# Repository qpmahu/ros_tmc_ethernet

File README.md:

# ros_tmc_ethernet
ROS node with ethernet TCP/UDP and TMC2208 via PIC18F24K50

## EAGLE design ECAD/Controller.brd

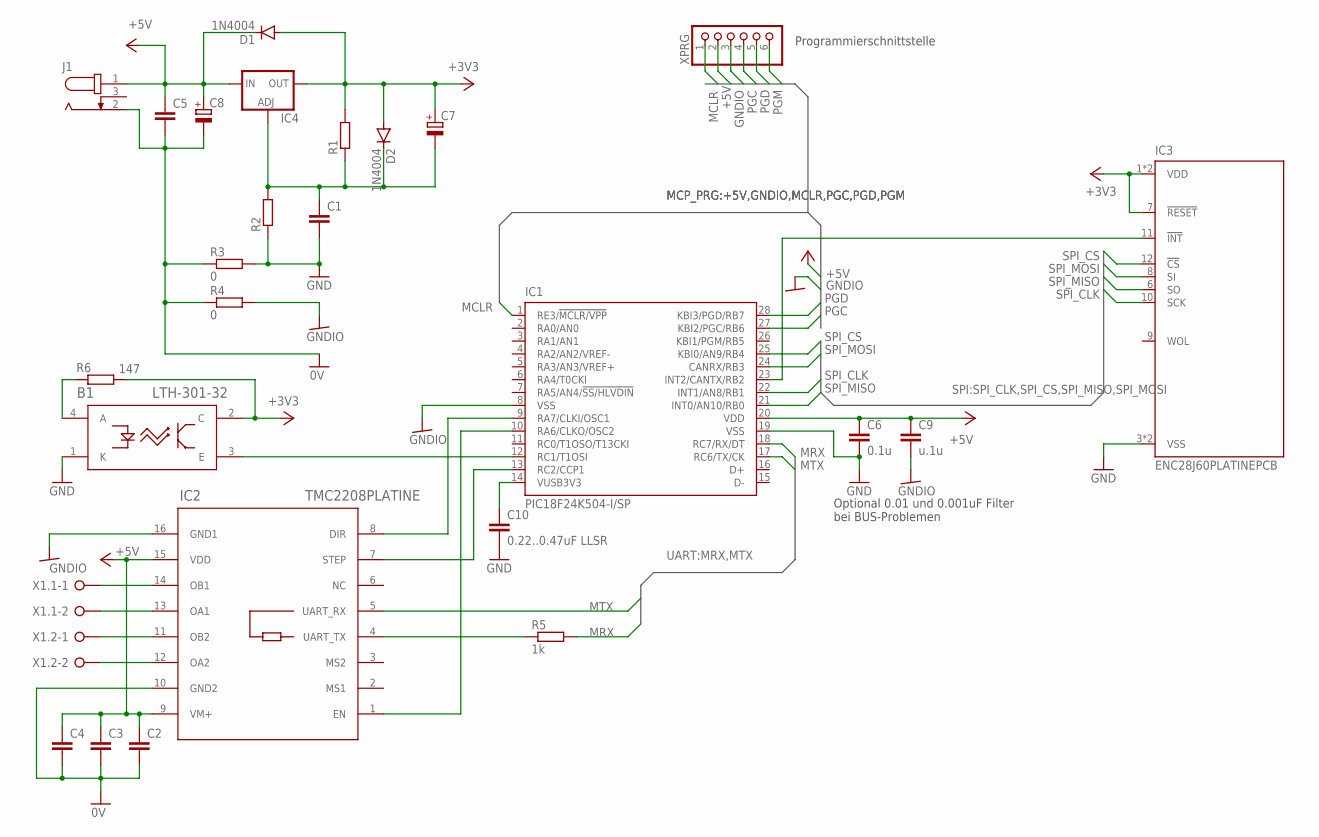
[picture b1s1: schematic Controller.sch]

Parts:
B1: LTH-301-32; LTH-301-32_LTO
C1, C2, C3, C4, C5: C-EU025_050-025X075; C025_050-025X075
C6: 0.1u; C025_050-025X075
C7, C8: CPOL-EUE2.5-6; E2,5-6
C9: u.1u; C025_050-025X075
C10: 0.22..0.47uF LLSR; C025_050-025X075
D1, D2: 1N4004; DO41-10
IC1: PIC18F24K504-I/SP; DIL28-3
IC2: TMC2208PLATINE; 2X08_TMCBOARD
IC3: ENC28J60PLATINEPCB; ENCPLATINE
IC4: LM317TO220; 317TL
J1: JACK-PLUG2,5; SPC4078
R1, R2: R-EU_0207/10; 0207/10
R3, R4: 0; R0603
R5: 1k; R0603
R6: 147; 0207/10
X1.1, X1.2: W237-02P; W237-132
XPRG: PINHD-1X6/90; 1X06/90

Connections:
0V: C2.2, C3.2, C4.2, C5.2, C8.-, IC2.10 (GND2), J1.2, R3.1, R4.1
+3V3: B1.2 (C), C7.+, D1.A, D2.A, IC3.1 (VDD), IC3.2 (VDD), IC3.7 (!RESET), IC4.2 (OUT), R1.2, R6.2
+5V: C2.1, C3.1, C4.1, C5.1, C6.1, C8.+, C9.1, D1.C, IC1.20 (VDD), IC2.9 (VM+), IC2.15 (VDD), IC4.3 (IN), J1.1, XPRG.2
GND: B1.1 (K), C1.2, C6.2, C10.2, IC1.19 (VSS), IC3.3 (VSS), IC3.4 (VSS), R2.1, R3.2
GNDIO: C9.2, IC1.8 (VSS), IC2.16 (GND1), R4.2, XPRG.3
MCLR: IC1.1 (RE3/!MCLR/VPP), XPRG.1
MRX: IC1.18 (RC7/RX/DT), R5.2
MTX: IC1.17 (RC6/TX/CK), IC2.5 (UART_RX)
unnamed: IC2.4 (UART_TX), R5.1
unnamed: IC1.13 (RC2/CCP1), IC2.7 (STEP)
unnamed: C1.1, C7.-, D2.C, IC4.1 (ADJ), R1.1, R2.2
unnamed: IC2.14 (OB1), X1.1.1
unnamed: IC1.23 (INT2/CANTX/RB2), IC3.11 (!INT)
unnamed: IC1.10 (RA6/CLKO/OSC2), IC2.1 (EN)
unnamed: IC1.9 (RA7/CLKI/OSC1), IC2.8 (DIR)
unnamed: IC2.13 (OA1), X1.1.2
unnamed: IC2.11 (OB2), X1.2.1
unnamed: IC2.12 (OA2), X1.2.2
unnamed: C10.1, IC1.14 (VUSB3V3)
unnamed: B1.3 (E), IC1.12 (RC1/T1OSI)
unnamed: B1.4 (A), R6.1
PGC: IC1.27 (KBI2/PGC/RB6), XPRG.4
PGD: IC1.28 (KBI3/PGD/RB7), XPRG.5
PGM: XPRG.6
SPI_CLK: IC1.22 (INT1/AN8/RB1), IC3.10 (SCK)
SPI_CS: IC1.25 (KBI0/AN9/RB4), IC3.12 (!CS)
SPI_MISO: IC1.21 (INT0/AN10/RB0), IC3.6 (SO)
SPI_MOSI: IC1.24 (CANRX/RB3), IC3.8 (SI)

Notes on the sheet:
Programmierschnittstelle
Optional 0.01 und 0.001uF Filter bei BUS-Problemen

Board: 2 copper layers, 27 parts (0 on the bottom side), 27 nets, no tracks yet.

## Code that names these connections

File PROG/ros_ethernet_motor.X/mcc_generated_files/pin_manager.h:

/**
  @Generated Pin Manager Header File

  @Company:
    Microchip Technology Inc.

  @File Name:
    pin_manager.h

  @Summary:
    This is the Pin Manager file generated using PIC10 / PIC12 / PIC16 / PIC18 MCUs

  @Description
    This header file provides APIs for driver for .
    Generation Information :
        Product Revision  :  PIC10 / PIC12 / PIC16 / PIC18 MCUs - 1.81.4
        Device            :  PIC18F24K50
        Driver Version    :  2.11
    The generated drivers are tested against the following:
        Compiler          :  XC8 2.20 and above
        MPLAB 	          :  MPLAB X 5.40	
*/

/*
    (c) 2018 Microchip Technology Inc. and its subsidiaries. 
    
    Subject to your compliance with these terms, you may use Microchip software and any 
    derivatives exclusively with Microchip products. It is your responsibility to comply with third party 
    license terms applicable to your use of third party software (including open source software) that 
    may accompany Microchip software.
    
    THIS SOFTWARE IS SUPPLIED BY MICROCHIP "AS IS". NO WARRANTIES, WHETHER 
    EXPRESS, IMPLIED OR STATUTORY, APPLY TO THIS SOFTWARE, INCLUDING ANY 
    IMPLIED WARRANTIES OF NON-INFRINGEMENT, MERCHANTABILITY, AND FITNESS 
    FOR A PARTICULAR PURPOSE.
    
    IN NO EVENT WILL MICROCHIP BE LIABLE FOR ANY INDIRECT, SPECIAL, PUNITIVE, 
    INCIDENTAL OR CONSEQUENTIAL LOSS, DAMAGE, COST OR EXPENSE OF ANY KIND 
    WHATSOEVER RELATED TO THE SOFTWARE, HOWEVER CAUSED, EVEN IF MICROCHIP 
    HAS BEEN ADVISED OF THE POSSIBILITY OR THE DAMAGES ARE FORESEEABLE. TO 
    THE FULLEST EXTENT ALLOWED BY LAW, MICROCHIP'S TOTAL LIABILITY ON ALL 
    CLAIMS IN ANY WAY RELATED TO THIS SOFTWARE WILL NOT EXCEED THE AMOUNT 
    OF FEES, IF ANY, THAT YOU HAVE PAID DIRECTLY TO MICROCHIP FOR THIS 
    SOFTWARE.
*/

#ifndef PIN_MANAGER_H
#define PIN_MANAGER_H

/**
  Section: Included Files
*/

#include <xc.h>

#define INPUT   1
#define OUTPUT  0

#define HIGH    1
#define LOW     0

#define ANALOG      1
#define DIGITAL     0

#define PULL_UP_ENABLED      1
#define PULL_UP_DISABLED     0

// get/set RB0 procedures
#define RB0_SetHigh()            do { LATBbits.LATB0 = 1; } while(0)
#define RB0_SetLow()             do { LATBbits.LATB0 = 0; } while(0)
#define RB0_Toggle()             do { LATBbits.LATB0 = ~LATBbits.LATB0; } while(0)
#define RB0_GetValue()              PORTBbits.RB0
#define RB0_SetDigitalInput()    do { TRISBbits.TRISB0 = 1; } while(0)
#define RB0_SetDigitalOutput()   do { TRISBbits.TRISB0 = 0; } while(0)
#define RB0_SetPullup()             do { WPUBbits.WPUB0 = 1; } while(0)
#define RB0_ResetPullup()           do { WPUBbits.WPUB0 = 0; } while(0)
#define RB0_SetAnalogMode()         do { ANSELBbits.ANSB0 = 1; } while(0)
#define RB0_SetDigitalMode()        do { ANSELBbits.ANSB0 = 0; } while(0)

// get/set RB1 procedures
#define RB1_SetHigh()            do { LATBbits.LATB1 = 1; } while(0)
#define RB1_SetLow()             do { LATBbits.LATB1 = 0; } while(0)
#define RB1_Toggle()             do { LATBbits.LATB1 = ~LATBbits.LATB1; } while(0)
#define RB1_GetValue()              PORTBbits.RB1
#define RB1_SetDigitalInput()    do { TRISBbits.TRISB1 = 1; } while(0)
#define RB1_SetDigitalOutput()   do { TRISBbits.TRISB1 = 0; } while(0)
#define RB1_SetPullup()             do { WPUBbits.WPUB1 = 1; } while(0)
#define RB1_ResetPullup()           do { WPUBbits.WPUB1 = 0; } while(0)
#define RB1_SetAnalogMode()         do { ANSELBbits.ANSB1 = 1; } while(0)
#define RB1_SetDigitalMode()        do { ANSELBbits.ANSB1 = 0; } while(0)

// get/set RB2 procedures
#define RB2_SetHigh()            do { LATBbits.LATB2 = 1; } while(0)
#define RB2_SetLow()             do { LATBbits.LATB2 = 0; } while(0)
#define RB2_Toggle()             do { LATBbits.LATB2 = ~LATBbits.LATB2; } while(0)
#define RB2_GetValue()              PORTBbits.RB2
#define RB2_SetDigitalInput()    do { TRISBbits.TRISB2 = 1; } while(0)
#define RB2_SetDigitalOutput()   do { TRISBbits.TRISB2 = 0; } while(0)
#define RB2_SetPullup()             do { WPUBbits.WPUB2 = 1; } while(0)
#define RB2_ResetPullup()           do { WPUBbits.WPUB2 = 0; } while(0)
#define RB2_SetAnalogMode()         do { ANSELBbits.ANSB2 = 1; } while(0)
#define RB2_SetDigitalMode()        do { ANSELBbits.ANSB2 = 0; } while(0)

// get/set RB3 procedures
#define RB3_SetHigh()            do { LATBbits.LATB3 = 1; } while(0)
#define RB3_SetLow()             do { LATBbits.LATB3 = 0; } while(0)
#define RB3_Toggle()             do { LATBbits.LATB3 = ~LATBbits.LATB3; } while(0)
#define RB3_GetValue()              PORTBbits.RB3
#define RB3_SetDigitalInput()    do { TRISBbits.TRISB3 = 1; } while(0)
#define RB3_SetDigitalOutput()   do { TRISBbits.TRISB3 = 0; } while(0)
#define RB3_SetPullup()             do { WPUBbits.WPUB3 = 1; } while(0)
#define RB3_ResetPullup()           do { WPUBbits.WPUB3 = 0; } while(0)
#define RB3_SetAnalogMode()         do { ANSELBbits.ANSB3 = 1; } while(0)
#define RB3_SetDigitalMode()        do { ANSELBbits.ANSB3 = 0; } while(0)

/**
   @Param
    none
   @Returns
    none
   @Description
    GPIO and peripheral I/O initialization
   @Example
    PIN_MANAGER_Initialize();
 */
void PIN_MANAGER_Initialize (void);

/**
 * @Param
    none
 * @Returns
    none
 * @Description
    Interrupt on Change Handling routine
 * @Example
    PIN_MANAGER_IOC();
 */
void PIN_MANAGER_IOC(void);



#endif // PIN_MANAGER_H
/**
 End of File
*/

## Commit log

2020-06-09 Added ECAD
2020-06-09 Daily ECAD clean up SW begin planning program contents & structure
2020-06-23 Make compileable with TCP and UDP, not compileable on chosen PIC18F24K50, need to change!
2020-06-24 Make compilable with TCP and UDP, Switched from PIC18F24K50 to PIC18F26K20 because of XC8 Standard compiler memory limit
2020-07-30 Reconfigure MCC, try to reduce memory load
2020-07-30 Fix Issues
2020-07-30 Fix Issues 2
2020-08-19 Restart with new controller PIC18F67K40
2020-08-20 Starting ECAD with new controller. Successfull compiled AN1921 TCP.

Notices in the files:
parts and their libraries:
COPYRIGHT: Copyright (C) 2018 Accelerated Designs. All rights reserved
